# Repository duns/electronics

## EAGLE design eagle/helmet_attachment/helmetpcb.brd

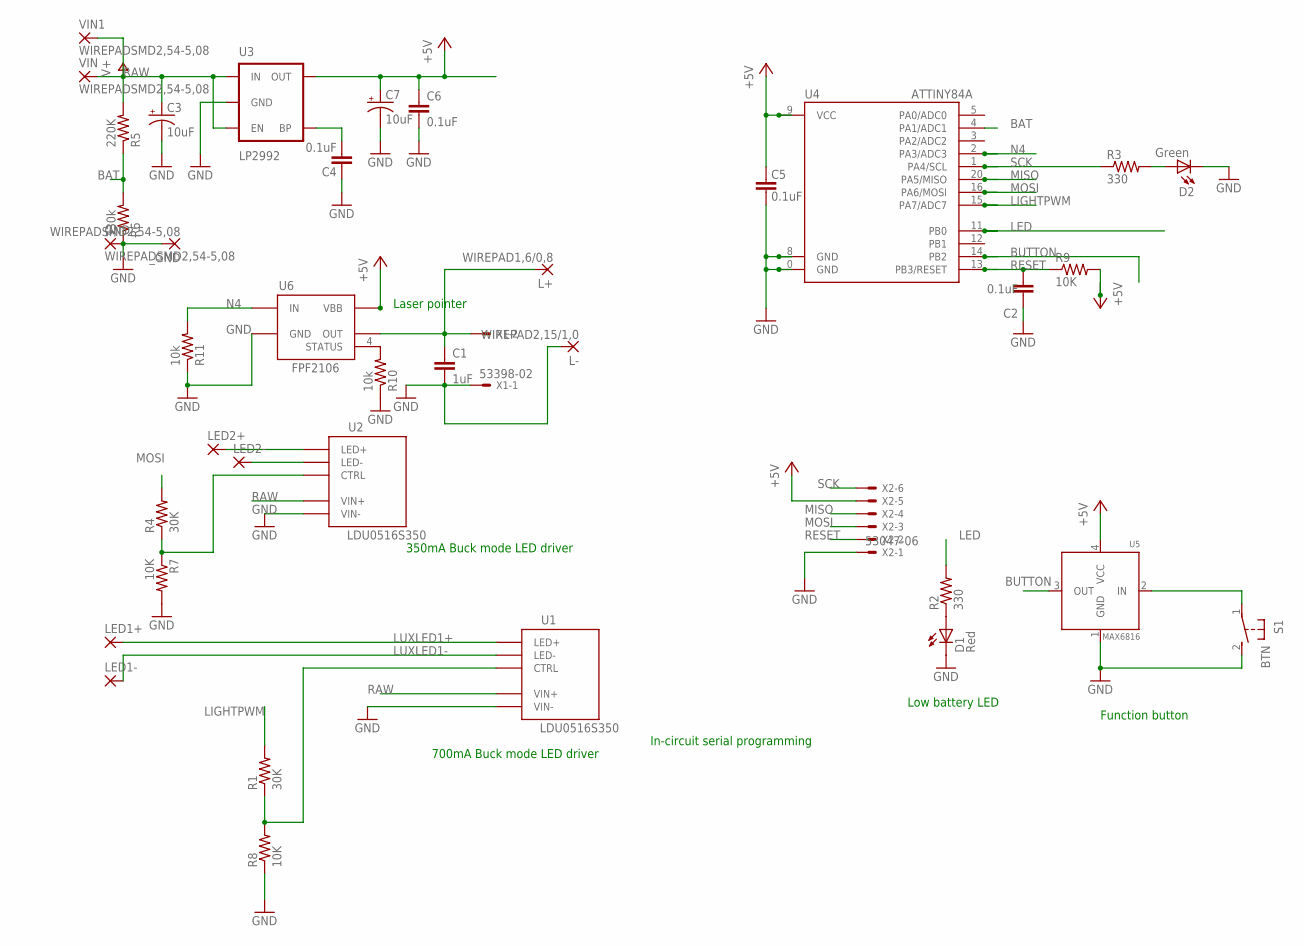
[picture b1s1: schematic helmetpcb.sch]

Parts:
C1: 1uF; C0603
C2, C4, C5, C6: 0.1uF; 0603
C3, C7: 10uF; EIA3216
D1: Red; LED-0603
D2: Green; LED-0603
GND: WIREPADSMD2,54-5,08; SMD2,54-5,08
L+: WIREPAD1,6/0,8; 1,6/0,8
L-: WIREPAD2,15/1,0; 2,15/1,0
LED1+, LED1-, LED2+, LED2-: WIREPADSMD2,54-5,08; SMD2,54-5,08
R1, R4: 30K; 0603
R2, R3: 330; 0603
R5: 220K; 0603
R6: 330k; 0603
R7, R8, R9: 10K; 0603
R10, R11: 10k; 0603
S1: BTN; B3F-31XX
U1, U2: LDU0516S350
U3: LP2992; SOT23-5
U4: ATTINY84A; QFN20
U5: MAX6816; SOT143
U6: FPF2106; SOT23-5
VIN, VIN1: WIREPADSMD2,54-5,08; SMD2,54-5,08
X1: 53398-02
X2: 53047-06
_GND: WIREPADSMD2,54-5,08; SMD2,54-5,08

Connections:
+5V: C5.2, C6.1, C7.A (+), R9.2, U3.5 (OUT), U4.9 (VCC), U5.4 (VCC), U6.1 (VBB), X2.5
BAT: R5.1, R6.2, U4.4 (PA1/ADC1)
BUTTON: U4.14 (PB2), U5.3 (OUT)
GND: C1.2, C2.2, C3.C (-), C4.2, C5.1, C6.2, C7.C (-), D1.C, D2.C, GND.1, L-.1, R6.1, R7.2, R8.1, R10.1, R11.1, S1.2 (S), U1.8 (VIN-), U2.8 (VIN-), U3.2 (GND), U4.0 (GND), U4.8 (GND), U5.1 (GND), U6.2 (GND), X1.1, X2.1, _GND.1
LED: R2.2, U4.11 (PB0)
LED+: LED2+.1, U2.4 (LED+)
LED-: LED2-.1, U2.5 (LED-)
LIGHTPWM: R1.2, U4.15 (PA7/ADC7)
LUXLED1+: LED1+.1, U1.4 (LED+)
LUXLED1-: LED1-.1, U1.5 (LED-)
MISO: U4.20 (PA5/MISO), X2.4
MOSI: R4.2, U4.16 (PA6/MOSI), X2.3
N4: R11.2, U4.2 (PA3/ADC3), U6.3 (IN)
unnamed: R1.1, R8.2, U1.7 (CTRL)
unnamed: D1.A, R2.1
unnamed: R10.2, U6.4 (STATUS)
unnamed: C1.1, L+.1, U6.5 (OUT), X1.2
unnamed: S1.1, U5.2 (IN)
unnamed: D2.A, R3.2
unnamed: R4.1, R7.1, U2.7 (CTRL)
unnamed: C4.1, U3.4 (BP)
RAW: C3.A (+), R5.2, U1.1 (VIN+), U2.1 (VIN+), U3.1 (IN), U3.3 (EN), VIN.1, VIN1.1
RESET: C2.1, R9.1, U4.13 (PB3/RESET), X2.2
SCK: R3.1, U4.1 (PA4/SCL), X2.6

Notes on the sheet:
Laser pointer
In-circuit serial programming
Low battery LED
Function button
700mA Buck mode LED driver
350mA Buck mode LED driver

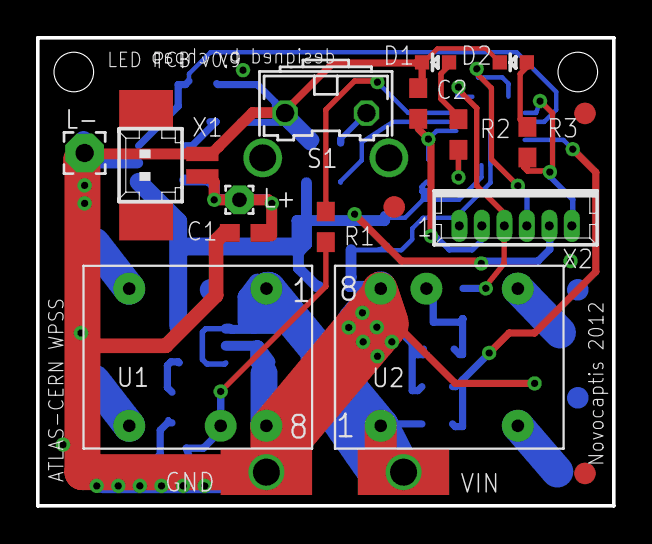
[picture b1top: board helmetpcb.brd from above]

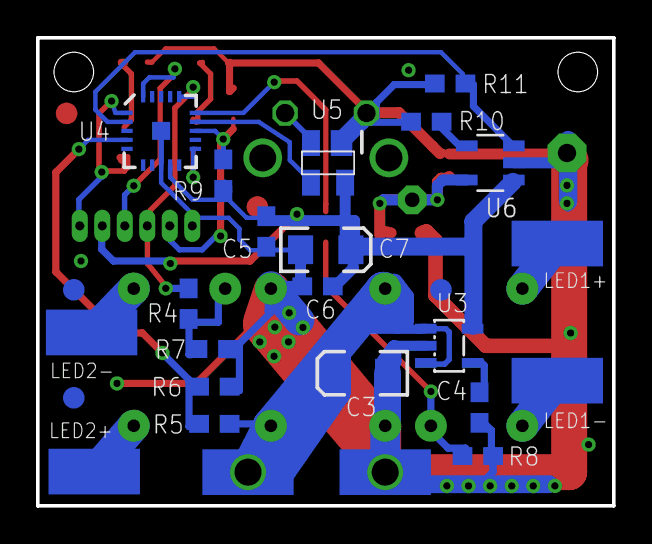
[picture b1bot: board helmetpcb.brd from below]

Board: 2 copper layers, 32.0 x 26.0 mm, 39 parts (23 on the bottom side), 24 nets.

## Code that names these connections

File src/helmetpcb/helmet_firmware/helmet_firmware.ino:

/*
attiny84
0->PB1
1->PB1
2->PB2
3->PA7
4->PA6
5->PA5
6->PA4
7->PA3
8->PA2
9->PA1
10->PA0
11?


   */
 
// Pin 13 has an LED connected on most Arduino boards.
// give it a name:
/*
#define LEDLEVEL0 255
#define LEDLEVEL1 180
#define LEDLEVEL2 90
#define LEDLEVEL3 0

*/

#define LEDLEVEL3 255
#define LEDLEVEL2 180
#define LEDLEVEL1 90
#define LEDLEVEL0 0


#define LEDCOUNTER 10
#define LONGBUTTONPRESS 1000
#define DEBOUNCEMS 10
int led = 6;
int btn  = 2;
int light1 = 3;
int light2 = 4;
int laser = 7;


int led2 = 0;

//int btn2  = 3;

unsigned char pwm  = 0;
volatile int state=0;
volatile int laserstate=0;
volatile int lightstate=0;
volatile int command_pending=0;
unsigned long timepressed;
unsigned long timediff;
volatile int ledstate=0;
volatile int ledstate2=0;
int ledcnt=LEDCOUNTER;

/*
void int0()
{
//     int val;
 //   state = !state;
 detachInterrupt(0);
  state=!digitalRead(btn);
    if(state)
    {
      timepressed=millis();
      digitalWrite(led,HIGH);
     attachInterrupt(0, int0, RISING);                     
    }
      else
      {
        timediff=millis()-timepressed;
      digitalWrite(led,LOW);
           command_pending=1;
      }
 
}
*/
void int0f()
{
//     int val;
 //   state = !state;
 detachInterrupt(0);
//  state=!digitalRead(btn2);
  timepressed=millis();
//   digitalWrite(led,HIGH);
   attachInterrupt(0, int0r, RISING);                     
   command_pending=1;
  
}

void toggle_led(int pinno,volatile int * state)
{
//       laserstate=!laserstate;
      if(!*state)
        digitalWrite(pinno,HIGH);
        else
          digitalWrite(pinno,LOW);
       *state=!*state;
}

void int0r()
{
//     int val;
 //   state = !state;
 detachInterrupt(0);
//  state=!digitalRead(btn2);
//    if(state)
//    {
        timediff=millis()-timepressed;
  //    digitalWrite(led,LOW);
      if(timediff>DEBOUNCEMS)
       command_pending=2;
       attachInterrupt(0, int0f, FALLING);
 
}

void btnpress()
{
//     val=digitalRead(btn);
      if(timediff<LONGBUTTONPRESS)
      {
        lightstate=++lightstate%4;
        switch(lightstate)
        {
          case 0:
        analogWrite(light2,LEDLEVEL0);
        analogWrite(light1,LEDLEVEL0);
          break;
          case 1:
        analogWrite(light2, LEDLEVEL1);
        analogWrite(light1, LEDLEVEL1);

          break;
          case 2:
        analogWrite(light2, LEDLEVEL2);
        analogWrite(light1, LEDLEVEL2);
          break;
          case 3:
//        digitalWrite(light2, HIGH);
//        digitalWrite(light1, HIGH);
        analogWrite(light2, LEDLEVEL3);
        analogWrite(light1, LEDLEVEL3);
          break;
/*          case 4:
        analogWrite(light2, LEDLEVEL3);
        analogWrite(light1, LEDLEVEL1);
          digitalWrite(light1,HIGH);
          break;
  */      }
      }
      else
      {
      toggle_led(led,&ledstate);      
      toggle_led(laser,&laserstate);
    }


    //  digitalWrite(led,HIGH);

}

// 9 ->Light2
//10 LASER
//11 LED
//12 PWM light 1
// the setup routine runs once when you press reset:
void setup() {                
  // initialize the digital pin as an output.
  digitalWrite(led, LOW);   // turn the LED on (HIGH is the voltage level)
 digitalWrite(light1, LOW);   // turn the LED on (HIGH is the voltage level)
 digitalWrite(laser, LOW);   // turn the LED on (HIGH is the voltage level)

  pinMode(led, OUTPUT);     
  pinMode(led2, OUTPUT);     
  pinMode(laser, OUTPUT);     
  pinMode(btn, INPUT);      
  digitalWrite(led, ledstate);   // turn the LED on (HIGH is the voltage level)
  digitalWrite(led2, ledstate2);   // turn the LED on (HIGH is the voltage level)
 digitalWrite(laser, LOW);   // turn the LED on (HIGH is the voltage level)

//   pinMode(light1, OUTPUT); 
  analogWrite(light1, LEDLEVEL0);
  analogWrite(light2, LEDLEVEL0);
  
// digitalWrite(light1, LOW);   // turn the LED on (HIGH is the voltage level)
 state=!digitalRead(btn);
//state=0;
 //int0();
 attachInterrupt(0, int0f, FALLING);
}

// the loop routine runs over and over again forever:
void loop() {
//    analogWrite(9, 60);
//  TCCR2A = _BV(COM2A1) | _BV(COM2B1) | _BV(WGM21) | _BV(WGM20);
//  TCCR2B = _BV(CS22);
//  OCR2A = 180;
//  OCR2B = 50;
  
//  digitalWrite(led, HIGH);   // turn the LED on (HIGH is the voltage level)
  delay(100);               // wait for a second
      if(command_pending==2)
      {
         btnpress();
          command_pending=0;
         
      }
      if(command_pending==1&&millis()-timepressed>LONGBUTTONPRESS)
        int0r();
      toggle_led(led2,&ledstate2);
      
//  digitalWrite(led, LOW);    // turn the LED off by making the voltage LOW
//  delay(500);               // wait for a second
}

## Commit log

2012-09-12 helmet PCB initial commit
2012-09-12 tidying
2012-09-12 gumstix related eagle library
2012-09-12 add .gitignore
2012-10-04 DRC for eurocircuits, changed component footprints
2012-10-05 Added firmware code. Finalized PCB for production
2012-10-05 Modified bill of materials
2012-10-06 Added Makefile and moved support libs for attiny84A into src dir
2012-10-08 final prototype v0.9
2012-10-25 added sleep mode and voltage check
2012-10-28 Overlay and stop-mask corrections
2012-10-28 Beta version of firmware
2013-12-05 Upgraded to version 1.05 of Arduino libraries
2013-12-05 Removed obsolete files
